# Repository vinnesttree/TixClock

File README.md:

# **TixClock**

The Tix Clock was originally sold in 2006 by ThinkGeek. Unfortunately, these are no longer sold. This project hopes to try to recreate this iconic clock in a miniature format.

# **TODO**
There are still things to do with this project which includes

 - Battery Management is not working
 - Encloser is not designed or tested

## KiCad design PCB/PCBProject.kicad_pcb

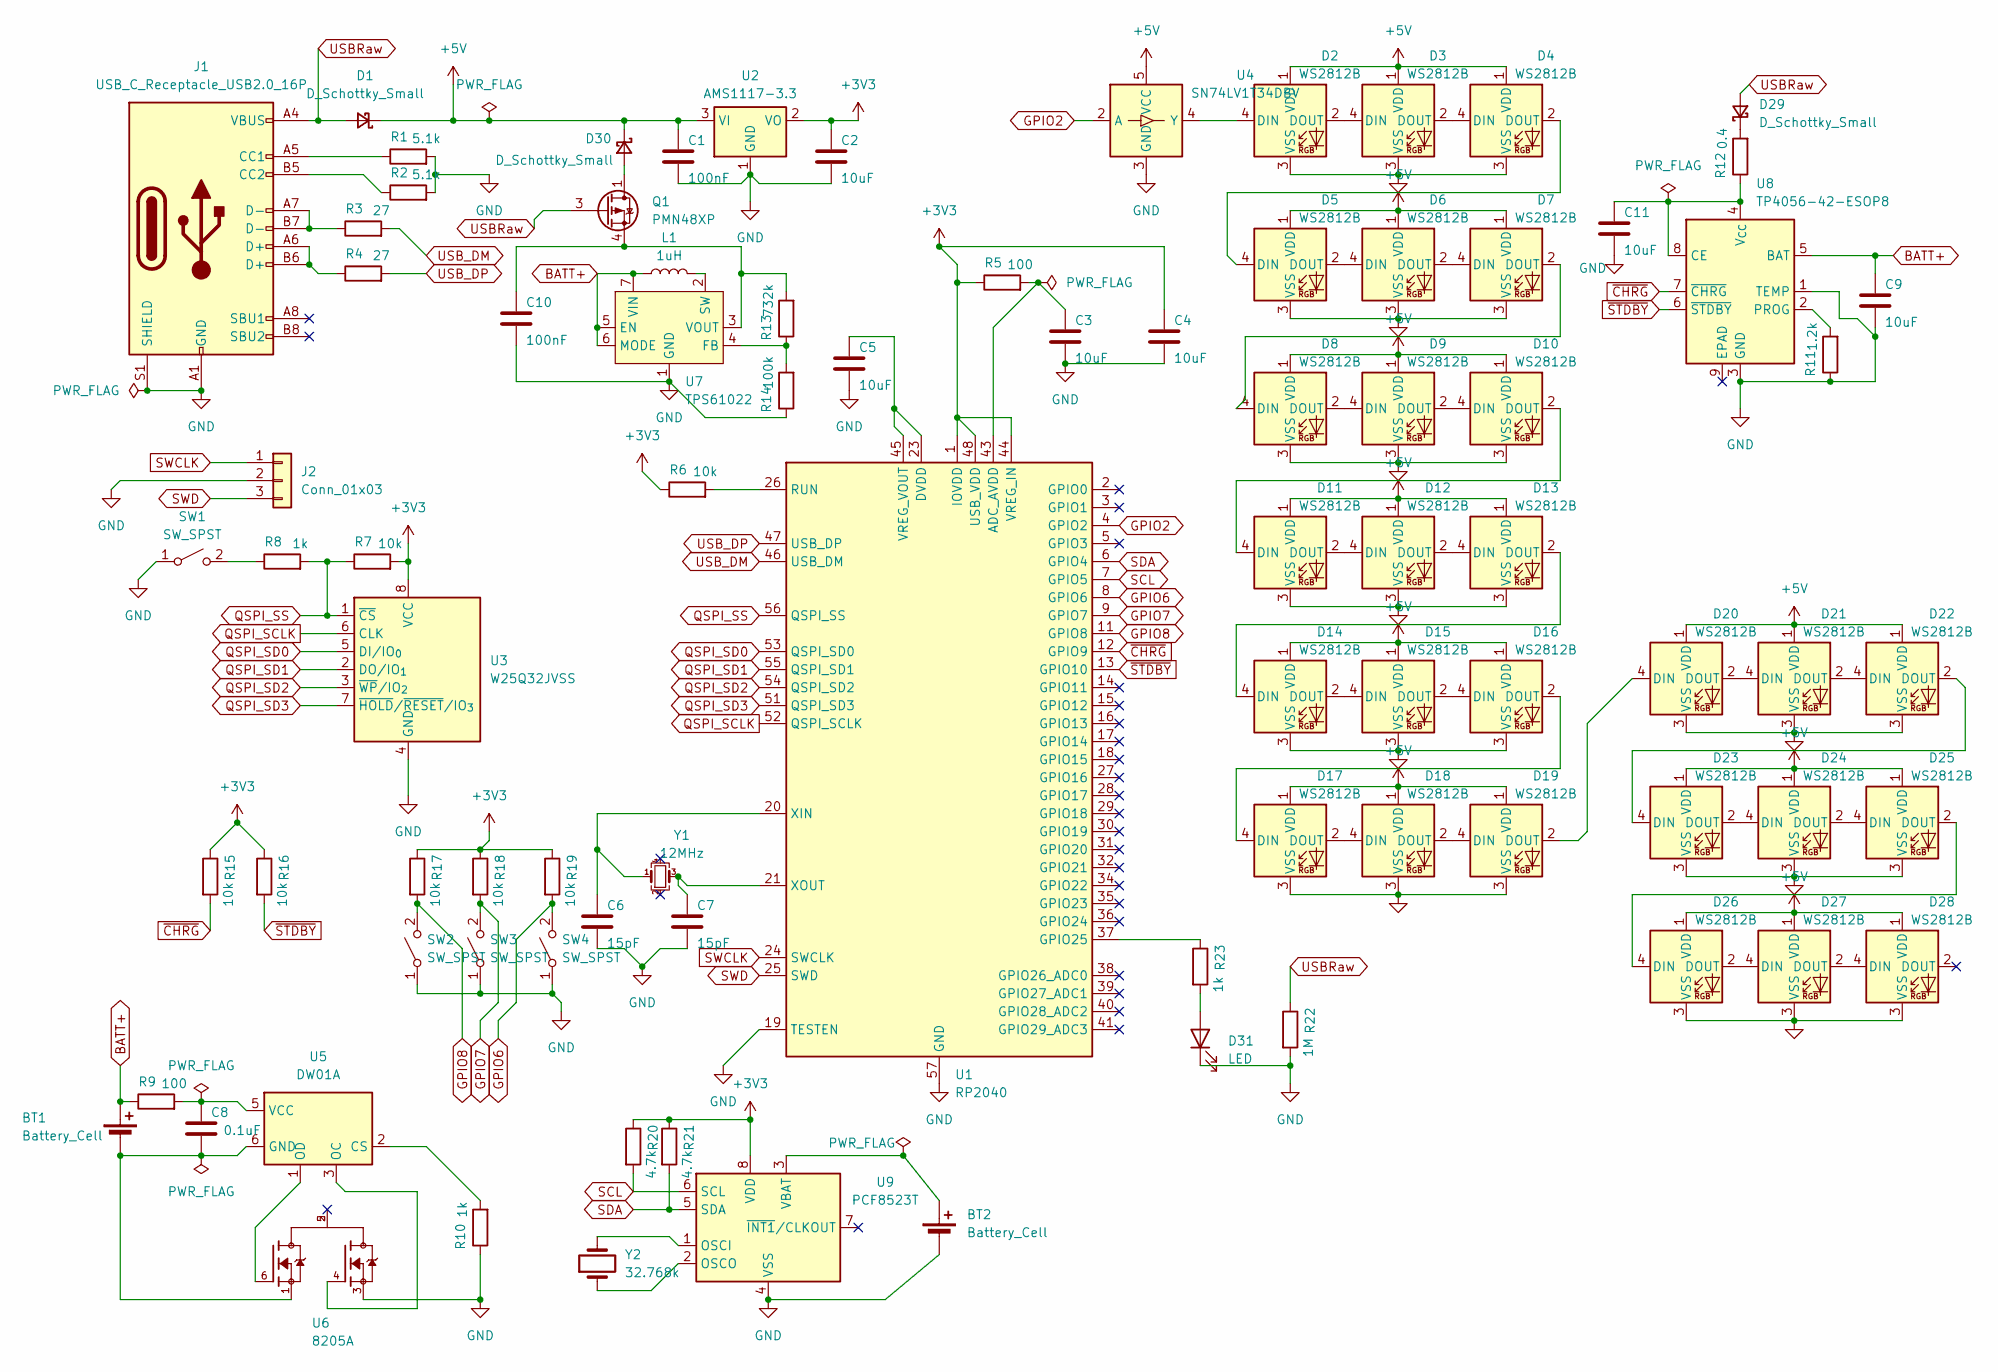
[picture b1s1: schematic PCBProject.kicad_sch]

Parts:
BT1: Battery_Cell; BatteryHolder_Keystone_1042_1x18650
BT2: Battery_Cell; BatteryHolder_Keystone_3034_1x20mm
C1, C10: 100nF; C_0805_2012Metric
C2, C3, C4, C5, C9, C11: 10uF; C_0805_2012Metric
C6, C7: 15pF; C_0805_2012Metric
C8: 0.1uF; C_0805_2012Metric
D1, D29, D30: D_Schottky_Small; D_SMA
D2, D3, D4, D5, D6, D7, D8, D9, D10, D11, D12, D13, D14, D15, D16, D17, D18, D19, D20, D21, D22, D23, D24, D25, D26, D27, D28: WS2812B; LED_WS2812B_PLCC4_5.0x5.0mm_P3.2mm
D31: LED; LED_0805_2012Metric
J1: USB_C_Receptacle_USB2.0_16P; USB_C_Receptacle_HRO_TYPE-C-31-M-12
J2: Conn_01x03; PinSocket_1x03_P2.54mm_Vertical
L1: 1uH; L_0805_2012Metric
Q1: PMN48XP; TSOP-6_1.65x3.05mm_P0.95mm
R1, R2: 5.1k; R_0805_2012Metric
R3, R4: 27; R_0805_2012Metric
R5, R9: 100; R_0805_2012Metric
R6, R7, R15, R16, R17, R18, R19: 10k; R_0805_2012Metric
R8, R10, R23: 1k; R_0805_2012Metric
R11: 1.2k; R_0805_2012Metric
R12: 0.4; R_0805_2012Metric
R13: 732k; R_0805_2012Metric
R14: 100k; R_0805_2012Metric
R20, R21: 4.7k; R_0805_2012Metric
R22: 1M; R_0805_2012Metric
SW1, SW2, SW3, SW4: SW_SPST; SW_SPST_CK_RS282G05A3
U1: RP2040; QFN-56-1EP_7x7mm_P0.4mm_EP3.2x3.2mm
U2: AMS1117-3.3; SOT-223-3_TabPin2
U3: W25Q32JVSS; SOIC-8_5.3x5.3mm_P1.27mm
U4: SN74LV1T34DBV; SOT-23-5
U5: DW01A; SOT-23-6
U6: 8205A; SOT95P285X140-6N; PARTREV NA
U7: TPS61022; Texas_RWU0007A_VQFN-7_2x2mm_P0.5mm
U8: TP4056-42-ESOP8; SOIC-8-1EP_3.9x4.9mm_P1.27mm_EP2.41x3.81mm
U9: PCF8523T; SOIC-8_3.9x4.9mm_P1.27mm
Y1: 12MHz; Crystal_SMD_SeikoEpson_FA238-4Pin_3.2x2.5mm
Y2: 32.768k

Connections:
+3V3: C2.1, C4.1, R5.1, R6.1, R7.2, R15.1, R16.1, R17.1, R18.1, R19.1, R20.1, R21.1, U1.1 (IOVDD), U1.10 (IOVDD), U1.22 (IOVDD), U1.33 (IOVDD), U1.42 (IOVDD), U1.44 (VREG_IN), U1.48 (USB_VDD), U1.49 (IOVDD), U2.2 (VO), U3.8 (VCC), U9.8 (VDD)
+5V: C1.1, D1.1 (K), D2.1 (VDD), D3.1 (VDD), D4.1 (VDD), D5.1 (VDD), D6.1 (VDD), D7.1 (VDD), D8.1 (VDD), D9.1 (VDD), D10.1 (VDD), D11.1 (VDD), D12.1 (VDD), D13.1 (VDD), D14.1 (VDD), D15.1 (VDD), D16.1 (VDD), D17.1 (VDD), D18.1 (VDD), D19.1 (VDD), D20.1 (VDD), D21.1 (VDD), D22.1 (VDD), D23.1 (VDD), D24.1 (VDD), D25.1 (VDD), D26.1 (VDD), D27.1 (VDD), D28.1 (VDD), D30.1 (K), U2.3 (VI), U4.5 (VCC)
BATT+: BT1.1 (+), C9.1, L1.1, R9.1, U7.5 (EN), U7.6 (MODE), U7.7 (VIN), U8.5 (BAT)
GND: BT2.2 (-), C1.2, C2.2, C3.2, C4.2, C5.2, C6.2, C7.2, C9.2, C10.2, C11.2, D2.3 (VSS), D3.3 (VSS), D4.3 (VSS), D5.3 (VSS), D6.3 (VSS), D7.3 (VSS), D8.3 (VSS), D9.3 (VSS), D10.3 (VSS), D11.3 (VSS), D12.3 (VSS), D13.3 (VSS), D14.3 (VSS), D15.3 (VSS), D16.3 (VSS), D17.3 (VSS), D18.3 (VSS), D19.3 (VSS), D20.3 (VSS), D21.3 (VSS), D22.3 (VSS), D23.3 (VSS), D24.3 (VSS), D25.3 (VSS), D26.3 (VSS), D27.3 (VSS), D28.3 (VSS), D31.1 (K), J1.A1 (GND), J1.A12 (GND), J1.B1 (GND), J1.B12 (GND), J1.S1 (SHIELD), J2.2, R1.2, R2.2, R10.1, R11.1, R14.1, R22.2, SW1.1 (A), SW2.1 (A), SW3.1 (A), SW4.1 (A), U1.19 (TESTEN), U1.57 (GND), U2.1 (GND), U3.4 (GND), U4.3 (GND), U6.3, U7.1 (GND), U8.1 (TEMP), U8.3 (GND), U9.4 (VSS)
GPIO2: U1.4 (GPIO2), U4.2 (A)
GPIO6: R19.2, SW4.2 (B), U1.8 (GPIO6)
GPIO7: R18.2, SW3.2 (B), U1.9 (GPIO7)
GPIO8: R17.2, SW2.2 (B), U1.11 (GPIO8)
unnamed: BT1.2 (-), C8.2, U5.6 (GND), U6.1
unnamed: BT2.1 (+), U9.3 (VBAT)
unnamed: D2.4 (DIN), U4.4 (Y)
unnamed: D2.2 (DOUT), D3.4 (DIN)
unnamed: D3.2 (DOUT), D4.4 (DIN)
unnamed: D4.2 (DOUT), D5.4 (DIN)
unnamed: D5.2 (DOUT), D6.4 (DIN)
unnamed: D6.2 (DOUT), D7.4 (DIN)
unnamed: D7.2 (DOUT), D8.4 (DIN)
unnamed: D8.2 (DOUT), D9.4 (DIN)
unnamed: D9.2 (DOUT), D10.4 (DIN)
unnamed: D10.2 (DOUT), D11.4 (DIN)
unnamed: D11.2 (DOUT), D12.4 (DIN)
unnamed: D12.2 (DOUT), D13.4 (DIN)
unnamed: D13.2 (DOUT), D14.4 (DIN)
unnamed: D14.2 (DOUT), D15.4 (DIN)
unnamed: D15.2 (DOUT), D16.4 (DIN)
unnamed: D16.2 (DOUT), D17.4 (DIN)
unnamed: D17.2 (DOUT), D18.4 (DIN)
unnamed: D18.2 (DOUT), D19.4 (DIN)
unnamed: D19.2 (DOUT), D20.4 (DIN)
unnamed: D20.2 (DOUT), D21.4 (DIN)
unnamed: D21.2 (DOUT), D22.4 (DIN)
unnamed: D22.2 (DOUT), D23.4 (DIN)
unnamed: D23.2 (DOUT), D24.4 (DIN)
unnamed: D24.2 (DOUT), D25.4 (DIN)
unnamed: D25.2 (DOUT), D26.4 (DIN)
unnamed: D26.2 (DOUT), D27.4 (DIN)
unnamed: D27.2 (DOUT), D28.4 (DIN)
unnamed: D29.1 (K), R12.2
unnamed: D30.2 (A), Q1.1 (D), Q1.2 (D), Q1.5 (D), Q1.6 (D)
unnamed: D31.2 (A), R23.2
unnamed: J1.A5 (CC1), R1.1
unnamed: J1.B5 (CC2), R2.1
unnamed: J1.A6 (D+), J1.B6 (D+), R4.1
unnamed: J1.A7 (D-), J1.B7 (D-), R3.1
unnamed: C10.1, Q1.4 (S), R13.2, U7.3 (VOUT)
unnamed: R8.1, SW1.2 (B)
unnamed: C3.1, R5.2, U1.43 (ADC_AVDD)
unnamed: R23.1, U1.37 (GPIO25)
unnamed: R6.2, U1.26 (RUN)
unnamed: C5.1, U1.23 (DVDD), U1.45 (VREG_VOUT), U1.50 (DVDD)
unnamed: C6.1, U1.20 (XIN), Y1.1
unnamed: C7.1, U1.21 (XOUT), Y1.3
unnamed: R10.2, U5.2 (CS)
unnamed: U5.3 (OC), U6.4
unnamed: U5.1 (OD), U6.6
unnamed: C8.1, R9.2, U5.5 (VCC)
unnamed: R13.1, R14.2, U7.4 (FB)
unnamed: L1.2, U7.2 (SW)
unnamed: C11.1, R12.1, U8.4 (V_{CC}), U8.8 (CE)
unnamed: R11.2, U8.2 (PROG)
unnamed: U9.2 (OSCO), Y2.1
unnamed: U9.1 (OSCI), Y2.2
QSPI_SCLK: U1.52 (QSPI_SCLK), U3.6 (CLK)
QSPI_SD0: U1.53 (QSPI_SD0), U3.5 (DI/IO_{0})
QSPI_SD1: U1.55 (QSPI_SD1), U3.2 (DO/IO_{1})
QSPI_SD2: U1.54 (QSPI_SD2), U3.3 (~WP/IO_{2})
QSPI_SD3: U1.51 (QSPI_SD3), U3.7 (~HOLD/~RESET/IO_{3})
QSPI_SS: R7.1, R8.2, U1.56 (QSPI_SS), U3.1 (~CS)
SCL: R20.2, U1.7 (GPIO5), U9.6 (SCL)
SDA: R21.2, U1.6 (GPIO4), U9.5 (SDA)
SWCLK: J2.1, U1.24 (SWCLK)
SWD: J2.3, U1.25 (SWD)
USBRaw: D1.2 (A), D29.2 (A), J1.A4 (VBUS), J1.A9 (VBUS), J1.B4 (VBUS), J1.B9 (VBUS), Q1.3 (G), R22.1
USB_DM: R3.2, U1.46 (USB_DM)
USB_DP: R4.2, U1.47 (USB_DP)
~CHRG: R15.2, U1.12 (GPIO9), U8.7 (~CHRG)
~STDBY: R16.2, U1.13 (GPIO10), U8.6 (~STDBY)

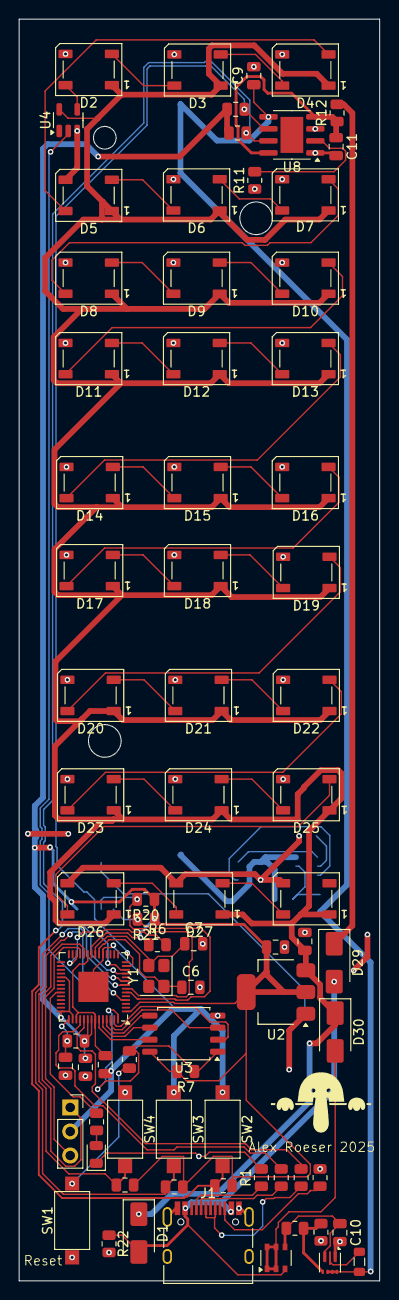
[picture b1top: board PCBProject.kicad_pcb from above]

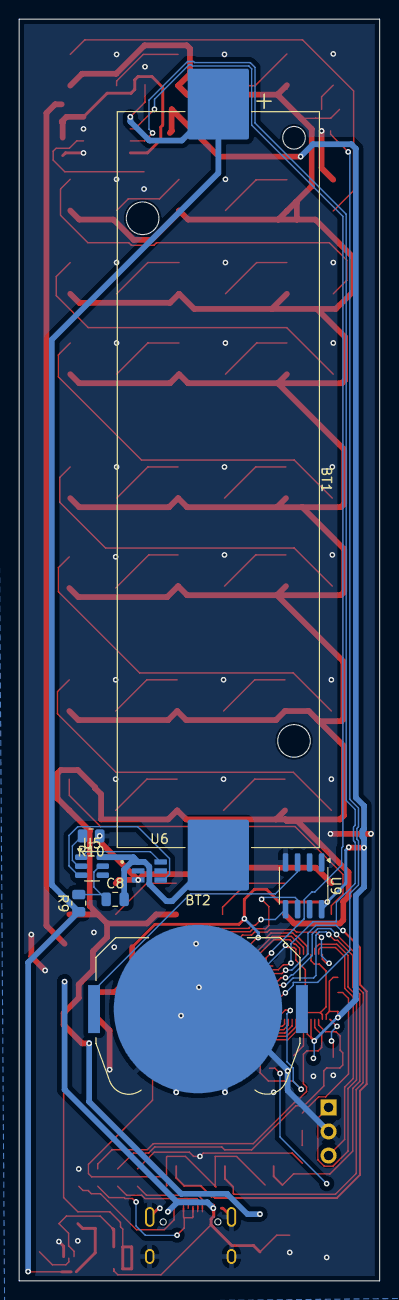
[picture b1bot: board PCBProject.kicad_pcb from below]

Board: 2 copper layers, 38.1 x 133.4 mm, 85 parts (8 on the bottom side), 75 nets.

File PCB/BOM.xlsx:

Id | Designator | Footprint | Quantity | Designation | Supplier and ref | Column1 | _1
1 | R23,R8,R10 | R_0805_2012Metric | 3 | 1k
2 | U8 | SOIC-8-1EP_3.9x4.9mm_P1.27mm_EP2.41x3.81mm | 1 | TP4056-42-ESOP8
3 | U7 | Texas_RWU0007A_VQFN-7_2x2mm_P0.5mm | 1 | TPS61022
4 | U1 | QFN-56-1EP_7x7mm_P0.4mm_EP3.2x3.2mm | 1 | RP2040
5 | BT1 | BatteryHolder_Keystone_1042_1x18650 | 1 | Battery_Cell
6 | D31 | LED_0805_2012Metric | 1 | LED
7 | D27,D11,D24,D14,D13,D5,D10,D25,D18,D19,D15,D12,D9,D3,D6,D28,D7,D20,D2,D4,D23,D2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 | LED_WS2812B_PLCC4_5.0x5.0mm_P3.2mm | 27 | WS2812B
8 | U4 | SOT-23-5 | 1 | SN74LV1T34DBV
9 | R1,R2 | R_0805_2012Metric | 2 | 5.1k
10 | R3,R4 | R_0805_2012Metric | 2 | 27
11 | C9,C4,C3,C11,C2,C5 | C_0805_2012Metric | 6 | 10uF
12 | R14 | R_0805_2012Metric | 1 | 100k
13 | R21,R20 | R_0805_2012Metric | 2 | 4.7k
14 | U3 | SOIC-8_5.3x5.3mm_P1.27mm | 1 | W25Q32JVSS
15 | SW2,SW4,SW1,SW3 | SW_SPST_CK_RS282G05A3 | 4 | SW_SPST
16 | D1,D30,D29 | D_SMA | 3 | D_Schottky_Small
17 | R18,R19,R16,R17,R7,R15,R6 | R_0805_2012Metric | 7 | 10k
18 | R13 | R_0805_2012Metric | 1 | 732k
19 | U2 | SOT-223-3_TabPin2 | 1 | AMS1117-3.3
20 | C1,C10 | C_0805_2012Metric | 2 | 100nF
21 | R11 | R_0805_2012Metric | 1 | 1.2k
22 | R5,R9 | R_0805_2012Metric | 2 | 100
23 | Q1 | TSOP-6_1.65x3.05mm_P0.95mm | 1 | PMN48XP
24 | J2 | PinSocket_1x03_P2.54mm_Vertical | 1 | Conn_01x03
25 | C6,C7 | C_0805_2012Metric | 2 | 15pF
26 | R12 | R_0805_2012Metric | 1 | 0.4
27 | Y1 | Crystal_SMD_SeikoEpson_FA238-4Pin_3.2x2.5mm | 1 | 12MHz
28 | R22 | R_0805_2012Metric | 1 | 1M
29 | L1 | L_0805_2012Metric | 1 | 1uH
30 | U6 | SOT95P285X140-6N | 1 | 8205A
31 | BT2 | BatteryHolder_Keystone_3034_1x20mm | 1 | Battery_Cell
32 | U5 | SOT-23-6 | 1 | DW01A
33 | C8 | C_0805_2012Metric | 1 | 0.1uF
34 | U9 | SOIC-8_3.9x4.9mm_P1.27mm | 1 | PCF8523T
35 | J1 | USB_C_Receptacle_HRO_TYPE-C-31-M-12 | 1 | USB_C_Receptacle_USB2.0_16P

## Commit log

2025-11-10 Removed redundant code
2025-11-10 Removed build files
2025-11-10 Changed gitIgnore
2025-11-13 Added PCB Files
2025-11-13 Added Readme
